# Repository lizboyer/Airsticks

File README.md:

# Airsticks-Advanced-Digital-Systems-Lab-Project
Airsticks was a project by myself (Elizabeth Boyer), Christian Tchilikov, and Dearborn Plys. It uses accelerometers, a speaker, an STM32 MCU, and a board we created. The user puts the velcro cuffs onto a pair of drum sticks and - based off of the orientation and acceleration of the sticks- can play through drumset samples.

# How To Use:
The project can be cloned onto the users local computer by running:
 “git clone https://github.com/lizboyer/Airsticks-Advanced-Digital-Systems-Lab-Project.git [name of new directory]” 
The “main” branch contains a directory called “10-6-sine,” which should be run via STM32CubeIDE on the STM32F407 Discovery Kit to playback the audio files of the drum noises.
The other directory, “firmware_with_directions_sound” should be run on the STM32G4 on our PCB.

If a serial device is used to read directional output, Picocom or Putty can be used to print those outputs via UART, at a baud rate of 19200.

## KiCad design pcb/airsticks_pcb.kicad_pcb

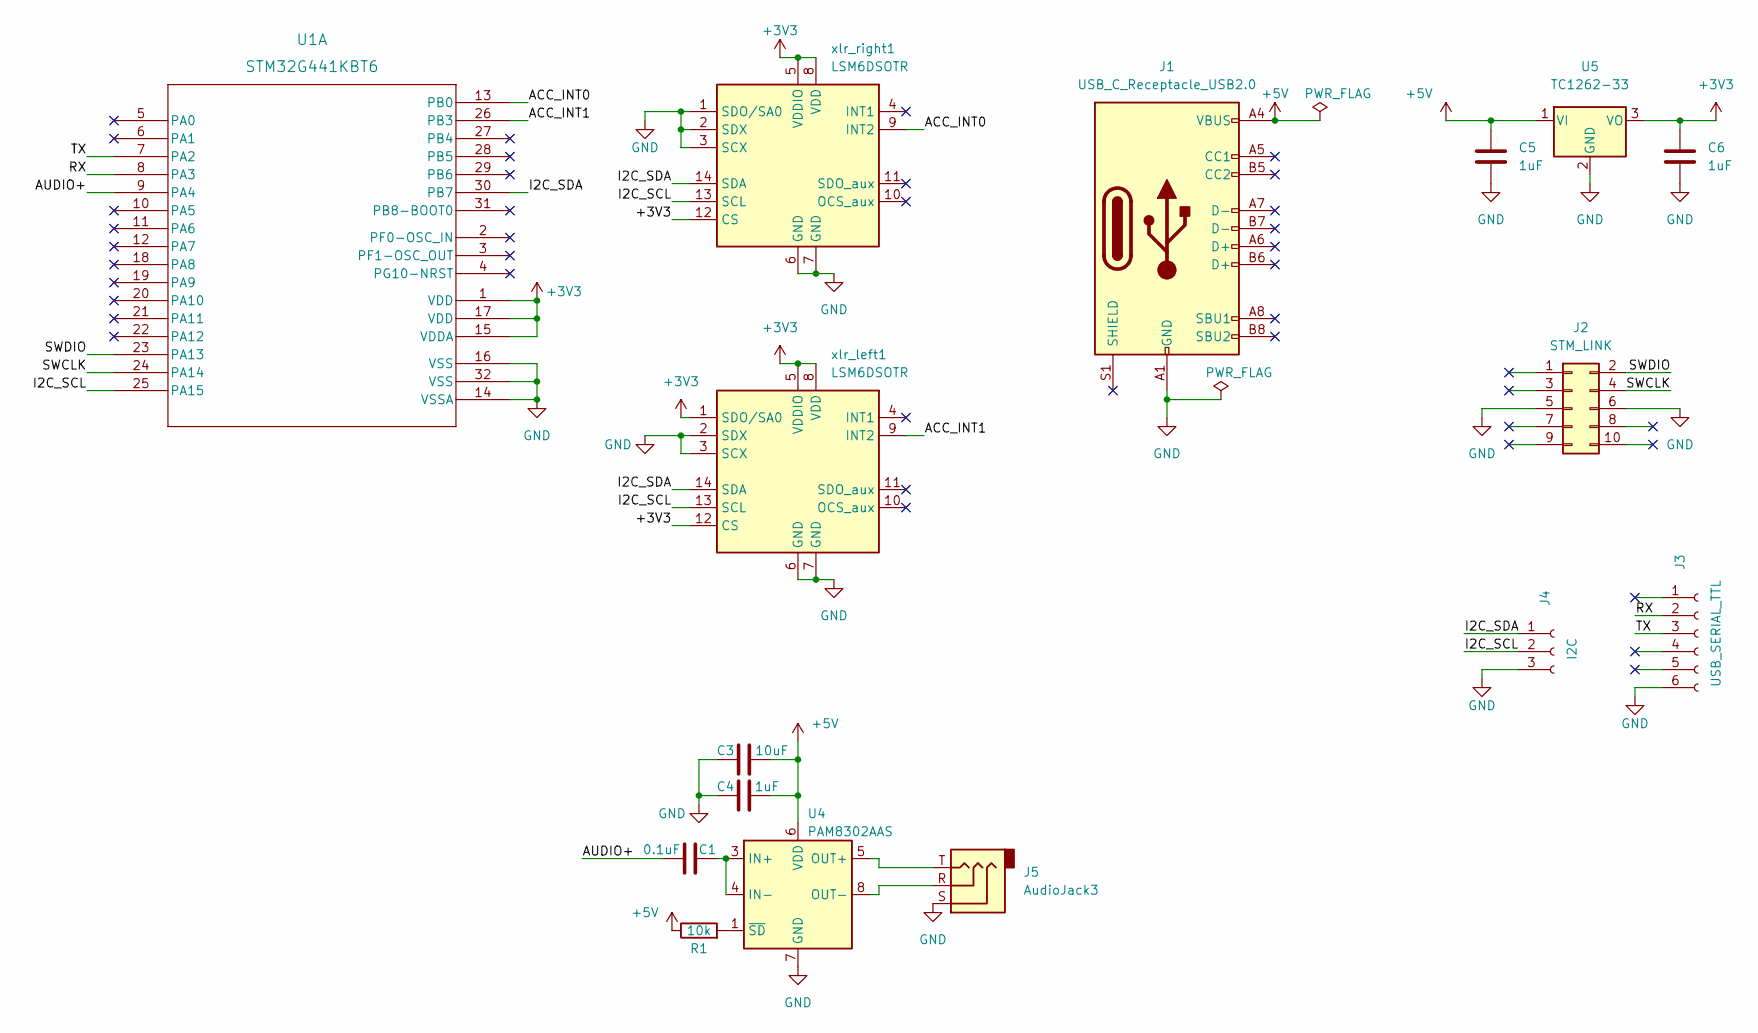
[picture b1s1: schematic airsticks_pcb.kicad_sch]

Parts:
C1: 0.1uF; C_0805_2012Metric_Pad1.18x1.45mm_HandSolder
C3: 10uF; C_0805_2012Metric_Pad1.18x1.45mm_HandSolder
C4, C5, C6: 1uF; C_0805_2012Metric_Pad1.18x1.45mm_HandSolder
J1: USB_C_Receptacle_USB2.0; USB_C_Receptacle_GCT_USB4085
J2: STM_LINK; PinHeader_2x05_P2.54mm_Vertical
J3: USB_SERIAL_TTL; PinHeader_1x06_P2.54mm_Vertical
J4: I2C; PinHeader_1x03_P2.54mm_Vertical
J5: AudioJack3; Jack_3.5mm_CUI_SJ-3523-SMT_Horizontal
R1: 10k; R_0805_2012Metric_Pad1.20x1.40mm_HandSolder
U1: STM32G441KBT6; STM32G441KBT6 LQFP-32
U4: PAM8302AAS; SO-8_3.9x4.9mm_P1.27mm
U5: TC1262-33; SOT-223-3_TabPin2
xlr_left1: LSM6DSOTR; LGA-14_3x2.5mm_P0.5mm_LayoutBorder3x4y
xlr_right1: LSM6DSOTR; LGA-14_3x2.5mm_P0.5mm_LayoutBorder3x4y

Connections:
+3V3: C6.1, U1.1 (VDD), U1.15 (VDDA), U1.17 (VDD), U5.3 (VO), xlr_left1.1 (SDO/SA0), xlr_left1.5 (VDDIO), xlr_left1.8 (VDD), xlr_left1.12 (CS), xlr_right1.5 (VDDIO), xlr_right1.8 (VDD), xlr_right1.12 (CS)
+5V: C3.2, C4.2, C5.1, J1.A4 (VBUS), J1.A9 (VBUS), J1.B4 (VBUS), J1.B9 (VBUS), R1.1, U4.6 (VDD), U5.1 (VI)
/ACC_INT0: U1.13 (PB0), xlr_right1.9 (INT2)
/ACC_INT1: U1.26 (PB3), xlr_left1.9 (INT2)
/AUDIO+: C1.1, U1.9 (PA4)
/I2C_SCL: J4.2, U1.25 (PA15), xlr_left1.13 (SCL), xlr_right1.13 (SCL); also elsewhere on the board
/I2C_SDA: J4.1, U1.30 (PB7), xlr_left1.14 (SDA), xlr_right1.14 (SDA); also elsewhere on the board
/RX: J3.2, U1.8 (PA3)
/SWCLK: J2.4, U1.24 (PA14)
/SWDIO: J2.2, U1.23 (PA13)
/TX: J3.3, U1.7 (PA2)
GND: C3.1, C4.1, C5.2, C6.2, J1.A1 (GND), J1.A12 (GND), J1.B1 (GND), J1.B12 (GND), J2.5, J2.6, J3.6, J4.3, J5.S, U1.14 (VSSA), U1.16 (VSS), U1.32 (VSS), U4.7 (GND), U5.2 (GND), xlr_left1.2 (SDX), xlr_left1.3 (SCX), xlr_left1.6 (GND), xlr_left1.7 (GND), xlr_right1.1 (SDO/SA0), xlr_right1.2 (SDX), xlr_right1.3 (SCX), xlr_right1.6 (GND), xlr_right1.7 (GND); also elsewhere on the board
unnamed: C1.2, U4.3 (IN+), U4.4 (IN-)
unnamed: J5.R, U4.8 (OUT-)
unnamed: J5.T, U4.5 (OUT+)
unnamed: R1.2, U4.1 (~SD)

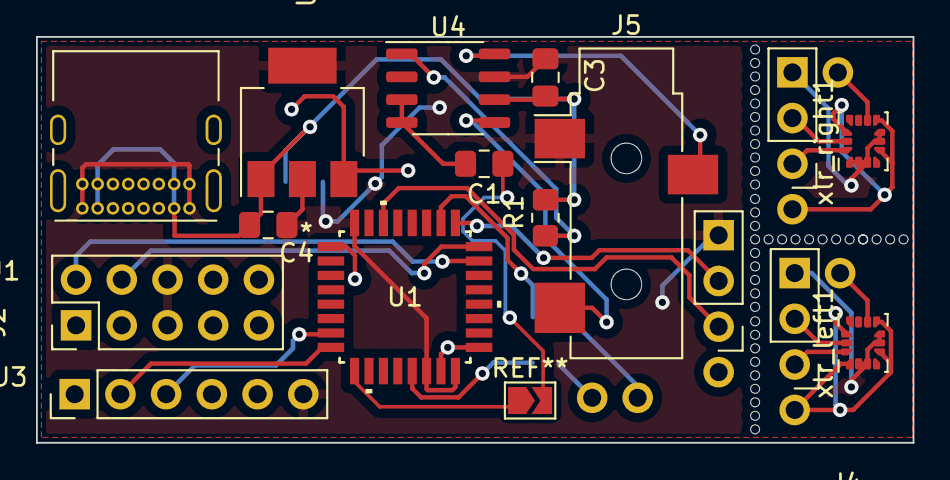
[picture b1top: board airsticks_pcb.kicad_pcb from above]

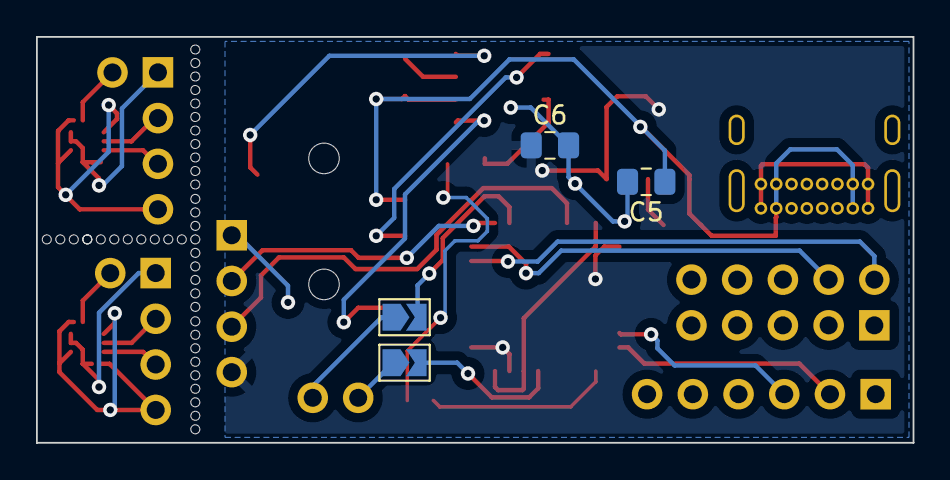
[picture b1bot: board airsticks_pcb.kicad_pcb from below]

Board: 2 copper layers, 48.7 x 22.5 mm, 18 parts (2 on the bottom side), 16 nets.

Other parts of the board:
J4#2, J4#3: I2C; PinHeader_1x03_P2.54mm_Vertical

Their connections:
/I2C_SCL: J4#3.2; also elsewhere on the board
/I2C_SDA: J4#2.1, J4#3.1; also elsewhere on the board
GND: J4#2.3, J4#3.3; also elsewhere on the board

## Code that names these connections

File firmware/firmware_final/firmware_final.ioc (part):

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Mcu.Name=STM32G441KBTx
Mcu.Package=LQFP32
Mcu.UserName=STM32G441KBTx
PA15.GPIOParameters=GPIO_Pu
PA15.GPIO_Pu=GPIO_PULLUP
PA15.Mode=I2C
PA15.Signal=I2C1_SCL
PA2.GPIOParameters=GPIO_PuPd
PA2.GPIO_PuPd=GPIO_PULLUP
PA2.Mode=Asynchronous
PA2.Signal=LPUART1_TX
PA3.GPIOParameters=GPIO_PuPd
PA3.GPIO_PuPd=GPIO_PULLUP
PA3.Mode=Asynchronous
PA3.Signal=LPUART1_RX
PA4.Signal=COMP_DAC11_group
PB0.Signal=GPIO_Input
PB3.Signal=GPIO_Input
PB7.GPIOParameters=GPIO_Pu
PB7.GPIO_Pu=GPIO_PULLUP
PB7.Mode=I2C
PB7.Signal=I2C1_SDA
RCC.HSE_VALUE=8000000
RCC.SYSCLKFreq_VALUE=64000000
RCC.SYSCLKSource=RCC_SYSCLKSOURCE_PLLCLK
board=custom

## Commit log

2023-09-03 395 Project Proposal
2023-09-06 KiCad Parts
2023-09-25 cleanup main
2023-10-03 got data output from accelerometer
2023-10-03 rewrote accelerometer interface for better organization
2023-10-04 got interrupts working, and added a test LED to turn on when accelerometer is upside down
2023-10-13 updated pcb
2023-10-13 fixed bug with accelerometer sending wrong irq info
2023-10-13 fixed small bug
2023-10-17 demo readyish
2023-10-17 expiramenting with serial output
2023-10-17 finished pcb
2023-10-18 small changes to final pcb layout
2023-10-19 pcb ready for printing
2023-10-24 updated accelerometer sensitivity to 8G
2023-10-25 file playback working (in 10-6 sine project)
2023-11-01 rotating through available sounds, no pop currently (in 10-6 sine project)
2023-11-01 Cleaned Acc with MLC
2023-11-03 Updated IOC, new MCU
2023-11-14 added testcode to for new mcu
2023-11-14 cleaned up old files
2023-11-30 new firmware versions
2023-12-01 push most recent firmware working
2023-12-02 new mcu in firmware_with_directions, has block that makes a jank sine wave in main
2023-12-03 timers work
2023-12-05 added sound version
2023-12-05 demo ready
2023-12-05 demo version 1 no double hit
2023-12-05 retriggerable gpio output from firmware_with_directions_sound
2023-12-05 adding sound V2 final
2023-12-05 sound and motion firmware added
2023-12-08 adding admin stuff
2023-12-13 updated PCB to reflect changes we made. NOTE: still need to make the boot0 change, as it is still currently floating
